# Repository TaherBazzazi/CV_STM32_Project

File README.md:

# Project Introduction
In this project, I presented my CV in a unique way to apply various embedded C tools.

## Project Objectives
The primary goal of this project was to showcase my skills in embedded C development, including the application of advanced techniques such as finite state machines and Xmacros.

#### State Machine:  
<div style="text-align:center;">
  
  </div>

## Hardware Used
- **Microcontroller**: STM32L432 Nucleo Board [Link](https://www.st.com/en/evaluation-tools/nucleo-l432kc.html)
- **Display**: Kuman 0.96 Inch OLED [Link](https://www.amazon.fr/dp/B01N2K3BC9?psc=1&ref=ppx_yo2ov_dt_b_product_details)
- **OLED Drivers**: [GitHub Repository](https://github.com/afiskon/stm32-ssd1306)

I also had the opportunity to design a PCB for this project using KiCad:

#### Schematic:  
<div style="text-align:center;">
   
  </div>

#### PCB 3D view:  
<div style="text-align:center;">
  
</div>

## Contact Information
If you would like to learn more about this project or get in touch with me, please feel free to do so through the following channels:
- [LinkedIn](https://www.linkedin.com/in/mohamed-taher-bazzazi-408395204/)
- Email: taher.bazzazi@ieee.org

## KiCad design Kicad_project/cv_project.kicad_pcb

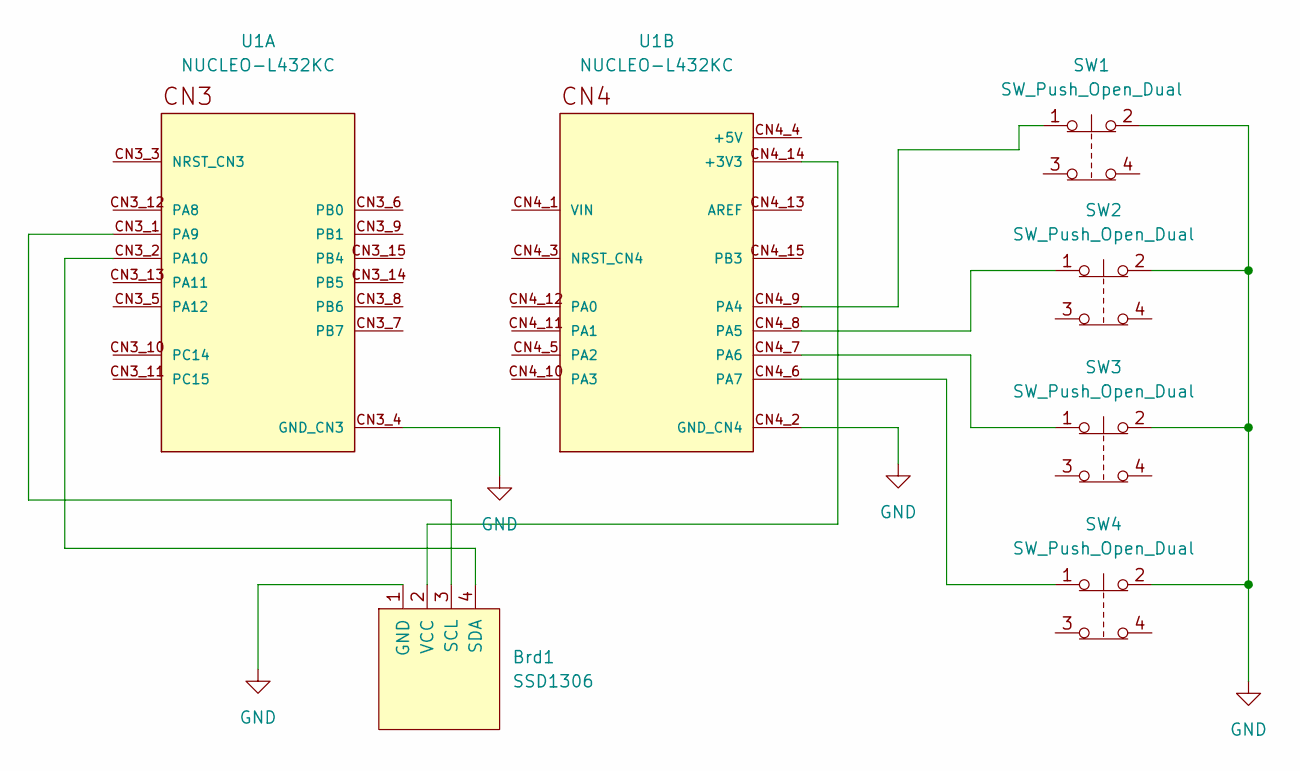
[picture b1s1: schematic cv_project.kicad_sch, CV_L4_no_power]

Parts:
Brd1: SSD1306; 128x64OLED
SW1, SW2, SW3, SW4: SW_Push_Open_Dual; 4pins_button
U1: NUCLEO-L432KC; MODULE_NUCLEO-L432KC; PARTREV N/A

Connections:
GND: Brd1.1 (GND), SW1.2, SW2.2, SW3.2, SW4.2, U1.CN3_4 (GND_CN3), U1.CN4_2 (GND_CN4)
unnamed: Brd1.3 (SCL), U1.CN3_1 (PA9)
unnamed: Brd1.4 (SDA), U1.CN3_2 (PA10)
unnamed: Brd1.2 (VCC), U1.CN4_14 (+3V3)
unnamed: SW1.1, U1.CN4_9 (PA4)
unnamed: SW2.1, U1.CN4_8 (PA5)
unnamed: SW3.1, U1.CN4_7 (PA6)
unnamed: SW4.1, U1.CN4_6 (PA7)

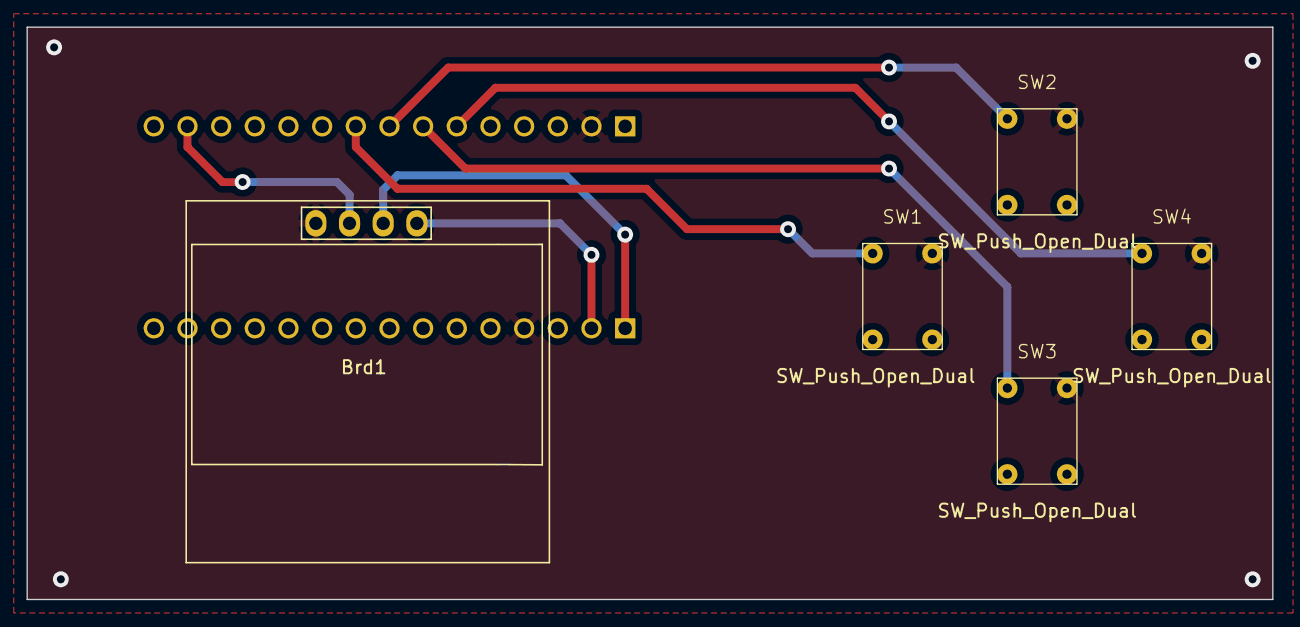
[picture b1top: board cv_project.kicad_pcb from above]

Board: 2 copper layers, 94.0 x 43.2 mm, 6 parts (1 on the bottom side), 8 nets.

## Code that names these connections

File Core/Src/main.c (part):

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	/* GPIO Ports Clock Enable */
	__HAL_RCC_GPIOA_CLK_ENABLE();

	/*Configure GPIO pins : PA4 PA5 PA6 PA7 */
	GPIO_InitStruct.Pin = GPIO_PIN_4|GPIO_PIN_5|GPIO_PIN_6|GPIO_PIN_7;
	GPIO_InitStruct.Mode = GPIO_MODE_IT_FALLING;
	GPIO_InitStruct.Pull = GPIO_PULLUP;
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
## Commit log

2023-09-25 kicad folder
2023-09-25 add schematic
2023-09-26 statemachine

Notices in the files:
Core/Src/main.c:
Copyright (c) 2023 STMicroelectronics.
All rights reserved.
This software is licensed under terms that can be found in the LICENSE file
